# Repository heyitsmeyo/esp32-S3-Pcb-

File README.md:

# This is a custom esp32-s3 pcb design : 

# Software Used for the design :  Kicad 

The pcb comes with 4 layers : The top and bottom layers are used for routing gpio pins with the mcu and other components ( resistors , capacitors , voltage regulator ...) , whereas the other two layers are used for setting GND plane and power routing.

# if you like the project , you can donate us for more : 

    https://ko-fi.com/heyitsmeyo

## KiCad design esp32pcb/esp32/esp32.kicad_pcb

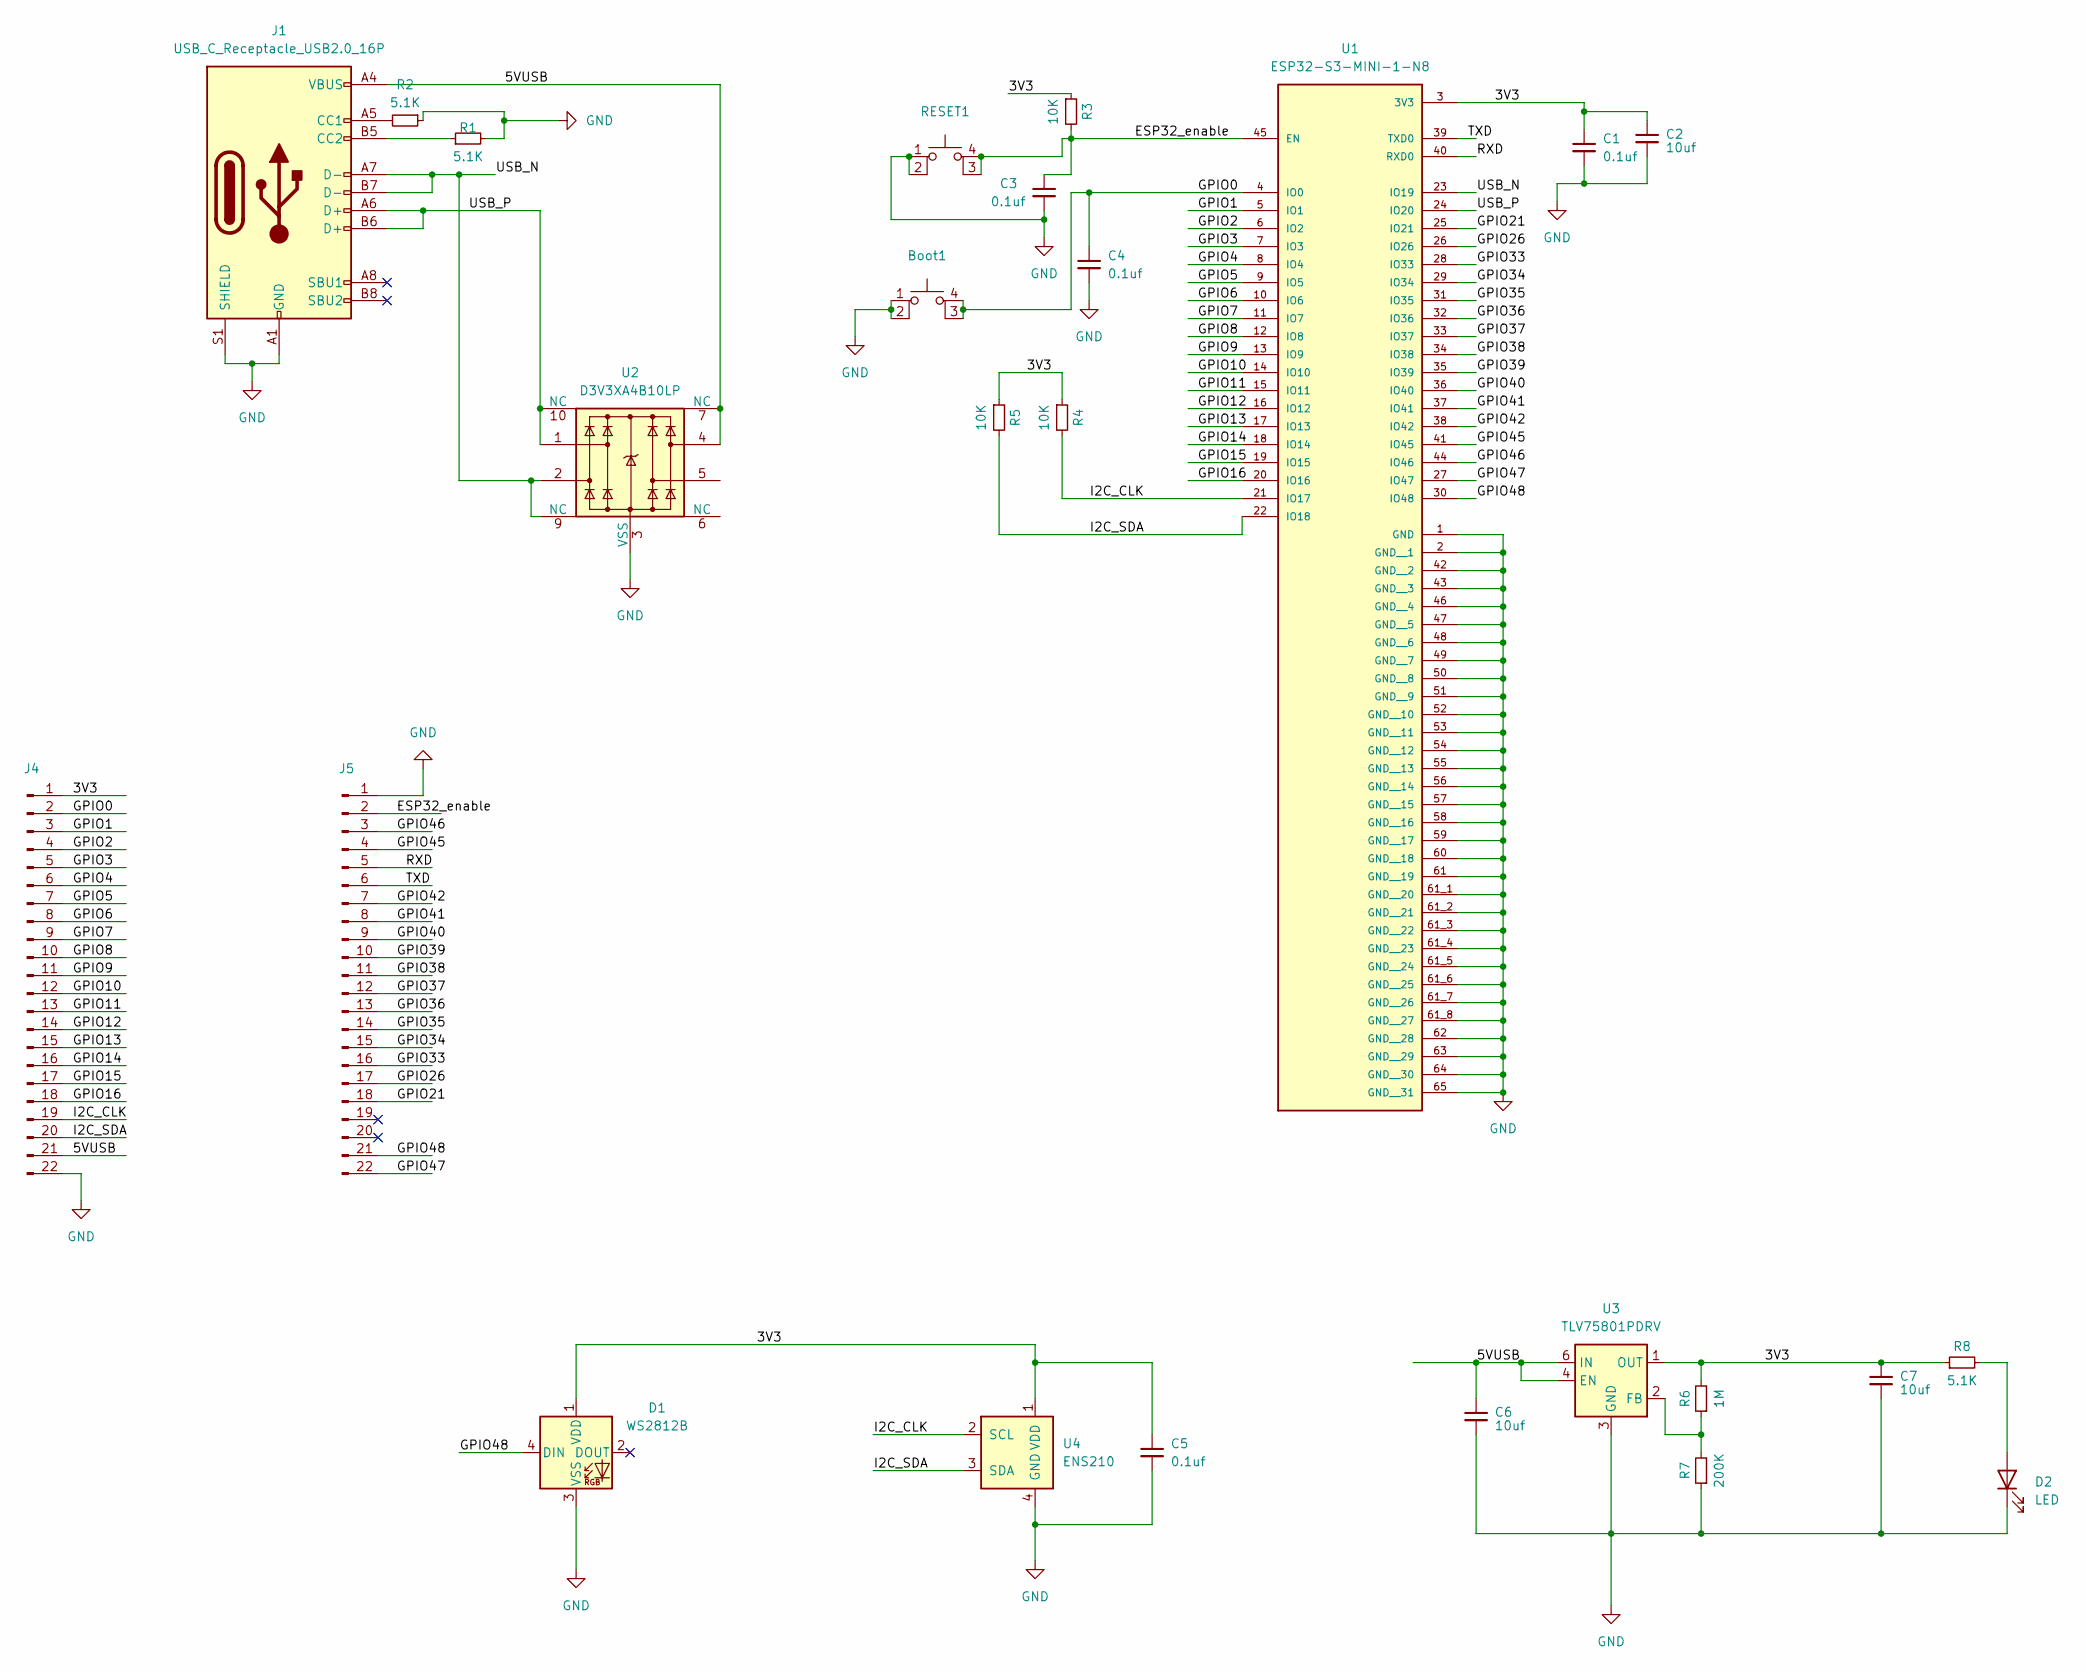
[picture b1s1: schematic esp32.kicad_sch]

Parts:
Boot1: SW_SPST_PTS810
C1, C3, C4, C5: 0.1uf; C_0201_0603Metric
C2, C6, C7: 10uf; C_0201_0603Metric
D1: WS2812B; LED_WS2812B_PLCC4_5.0x5.0mm_P3.2mm
D2: LED; D_0201_0603Metric
J1: USB_C_Receptacle_USB2.0_16P; USB_C_Receptacle_GCT_USB4105-xx-A_16P_TopMnt_Horizontal
J4, J5: PinHeader_1x22_P2.54mm_Vertical
R1, R2, R8: 5.1K; R_0603_1608Metric
R3, R4, R5: 10K; R_0603_1608Metric
R6: 1M; R_0603_1608Metric
R7: 200K; R_0603_1608Metric
RESET1: SW_SPST_PTS810
U1: ESP32-S3-MINI-1-N8; XCVR_ESP32-S3-MINI-1-N8; PARTREV v0.6
U2: D3V3XA4B10LP; Diodes_UDFN-10_1.0x2.5mm_P0.5mm
U3: TLV75801PDRV; WSON-6-1EP_2x2mm_P0.65mm_EP1x1.6mm
U4: ENS210; AMS_QFN-4-1EP_2x2mm_P0.95mm_EP0.7x1.6mm

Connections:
/3V3: C1.1, C2.1, C5.1, C7.1, D1.1 (VDD), J4.1, R3.1, R4.1, R5.1, R6.2, R8.1, U1.3 (3V3), U3.1 (OUT), U4.1 (VDD)
/5VUSB: C6.1, J1.A4 (VBUS), J1.A9 (VBUS), J1.B4 (VBUS), J1.B9 (VBUS), J4.21, U2.4, U2.7 (NC), U3.4 (EN), U3.6 (IN)
/ESP32_enable: C3.1, J5.2, R3.2, RESET1.3 (K), RESET1.4 (A), U1.45 (EN); also elsewhere on the board
/GPIO0: Boot1.3 (K), Boot1.4 (A), C4.1, J4.2, U1.4 (IO0)
/GPIO1: J4.3, U1.5 (IO1)
/GPIO2: J4.4, U1.6 (IO2)
/GPIO3: J4.5, U1.7 (IO3)
/GPIO4: J4.6, U1.8 (IO4)
/GPIO5: J4.7, U1.9 (IO5)
/GPIO6: J4.8, U1.10 (IO6)
/GPIO7: J4.9, U1.11 (IO7)
/GPIO8: J4.10, U1.12 (IO8)
/GPIO9: J4.11, U1.13 (IO9)
/GPIO10: J4.12, U1.14 (IO10)
/GPIO11: J4.13, U1.15 (IO11)
/GPIO12: J4.14, U1.16 (IO12)
/GPIO13: J4.15, U1.17 (IO13)
/GPIO14: J4.16, U1.18 (IO14)
/GPIO15: J4.17, U1.19 (IO15)
/GPIO16: J4.18, U1.20 (IO16)
/GPIO21: J5.18, U1.25 (IO21)
/GPIO26: J5.17, U1.26 (IO26)
/GPIO33: J5.16, U1.28 (IO33)
/GPIO34: J5.15, U1.29 (IO34)
/GPIO35: J5.14, U1.31 (IO35)
/GPIO36: J5.13, U1.32 (IO36)
/GPIO37: J5.12, U1.33 (IO37)
/GPIO38: J5.11, U1.34 (IO38)
/GPIO39: J5.10, U1.35 (IO39)
/GPIO40: J5.9, U1.36 (IO40)
/GPIO41: J5.8, U1.37 (IO41)
/GPIO42: J5.7, U1.38 (IO42)
/GPIO45: J5.4, U1.41 (IO45)
/GPIO46: J5.3, U1.44 (IO46)
/GPIO47: J5.22, U1.27 (IO47)
/GPIO48: D1.4 (DIN), J5.21, U1.30 (IO48)
/I2C_CLK: J4.19, R4.2, U1.21 (IO17), U4.2 (SCL)
/I2C_SDA: J4.20, R5.2, U1.22 (IO18), U4.3 (SDA)
/RXD: J5.5, U1.40 (RXD0)
/TXD: J5.6, U1.39 (TXD0)
/USB_N: J1.A7 (D-), J1.B7 (D-), U1.23 (IO19), U2.2, U2.9 (NC)
/USB_P: J1.A6 (D+), J1.B6 (D+), U1.24 (IO20), U2.1, U2.10 (NC)
GND: Boot1.1, Boot1.2, C1.2, C2.2, C3.2, C4.2, C5.2, C6.2, C7.2, D1.3 (VSS), D2.1 (K), J1.A1 (GND), J1.A12 (GND), J1.B1 (GND), J1.B12 (GND), J1.S1 (SHIELD), J4.22, J5.1, R1.2, R2.1, R7.1, RESET1.1, RESET1.2, U1.1 (GND), U1.2 (GND__1), U1.42 (GND__2), U1.43 (GND__3), U1.46 (GND__4), U1.47 (GND__5), U1.48 (GND__6), U1.49 (GND__7), U1.50 (GND__8), U1.51 (GND__9), U1.52 (GND__10), U1.53 (GND__11), U1.54 (GND__12), U1.55 (GND__13), U1.56 (GND__14), U1.57 (GND__15), U1.58 (GND__16), U1.59 (GND__17), U1.60 (GND__18), U1.61 (GND__19), U1.61_1 (GND__20), U1.61_2 (GND__21), U1.61_3 (GND__22), U1.61_4 (GND__23), U1.61_5 (GND__24), U1.61_6 (GND__25), U1.61_7 (GND__26), U1.61_8 (GND__27), U1.62 (GND__28), U1.63 (GND__29), U1.64 (GND__30), U1.65 (GND__31), U2.3 (VSS), U2.8 (VSS), U3.3 (GND), U3.7 (GND), U4.4 (GND), U4.5 (GND); also elsewhere on the board
unnamed: D2.2 (A), R8.2
unnamed: J1.A5 (CC1), R2.2
unnamed: J1.B5 (CC2), R1.1
unnamed: R6.1, R7.2, U3.2 (FB)

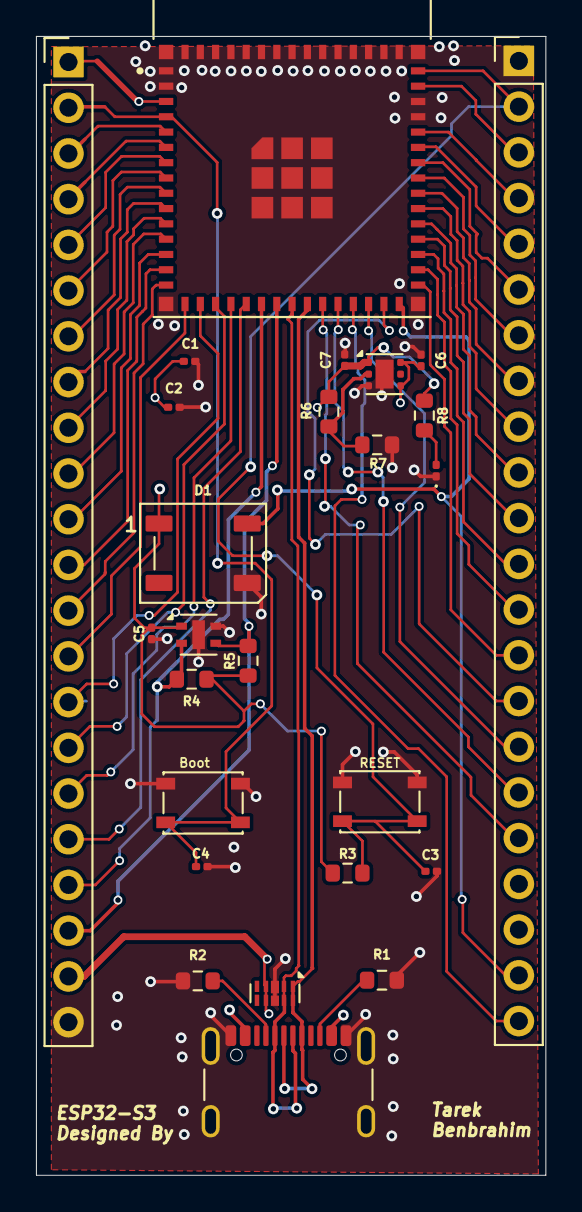
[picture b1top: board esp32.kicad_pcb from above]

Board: 4 copper layers, 28.3 x 63.3 mm, 26 parts (0 on the bottom side), 47 nets.

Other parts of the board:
RESET: SW_SPST_PTS810

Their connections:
/ESP32_enable: RESET.3 (K), RESET.4 (A); also elsewhere on the board
GND: RESET.1, RESET.2; also elsewhere on the board
